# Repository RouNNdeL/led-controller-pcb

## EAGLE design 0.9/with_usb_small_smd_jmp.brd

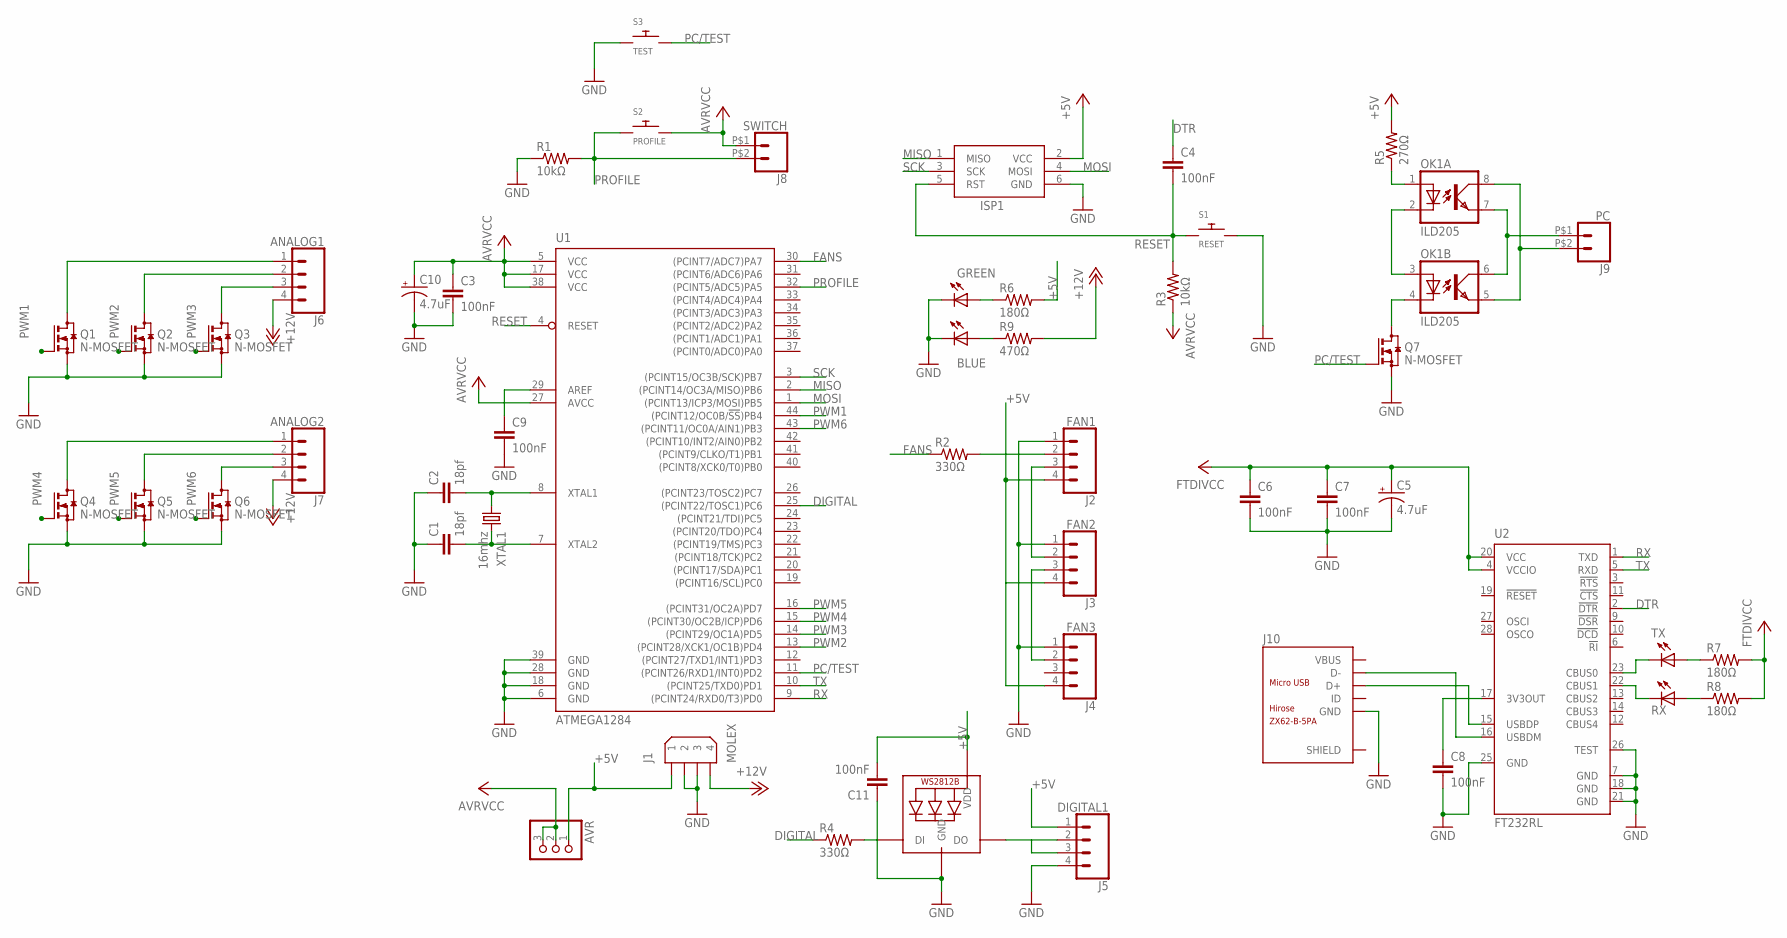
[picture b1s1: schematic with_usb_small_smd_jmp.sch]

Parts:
AVR: PINHD-1X3; 1X03
C1, C2: 18pf; C0805
C3, C4, C6, C7, C8, C9, C11: 100nF; C0805
C5, C10: 4.7uF; 153CLV-0405
ISP1: AVRISP-6; AVRISP
J1: MOLEX; 9090-4R
J2: FAN1; TJC8-4P
J3: FAN2; TJC8-4P
J4: FAN3; TJC8-4P
J5: DIGITAL1; MX-22-05-3041
J6: ANALOG1; MX-22-05-3041
J7: ANALOG2; MX-22-05-3041
J8: SWITCH; MX-7395-02BG
J9: PC; MX-7395-02BG
J10: MICRO_USB
LED1: TX; SML0805
LED2: RX; SML0805
LED3: GREEN; SML0805
LED4: BLUE; SML0805
OK1: ILD205; SOIC08
Q1, Q2, Q3, Q4, Q5, Q6, Q7: N-MOSFET; SOT23
R1, R3: 10kΩ; R0805
R2, R4: 330Ω; R0805
R5: 270Ω; R0805
R6, R7, R8: 180Ω; R0805
R9: 470Ω; R0805
RGB: WS2812B
S1: RESET; B3F-1000
S2: PROFILE; B3F-1000
S3: TEST; B3F-1000
U1: ATMEGA1284; TQFP44
U2: FT232RL; SSOP28
XTAL1: 16mhz; HC49U-V

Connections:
+3V3: C8.1, U2.17 (3V3OUT)
+5V: AVR.1, C5.+, C6.1, C7.1, C11.2, J1.1, J2.4, J3.4, J4.4, J5.1, R5.2, R6.2, R7.2, R8.2, RGB.1-VDD (VDD), U2.4 (VCCIO), U2.20 (VCC)
+12V: J1.4, J6.4, J7.4, R9.2
AVR: AVR.2, AVR.3, C3.1, C10.+, ISP1.2 (VCC), J8.P$1 (1), R3.1, S2.3, S2.4, U1.5 (VCC), U1.17 (VCC), U1.27 (AVCC), U1.38 (VCC)
D+: J10.3 (D+), U2.15 (USBDP)
D-: J10.2 (D-), U2.16 (USBDM)
DIGITAL: R4.1, U1.25 ((PCINT22/TOSC1)PC6)
DIN-D: J5.2, J5.3, RGB.2-DOUT (DO)
DTR: C4.1, U2.2 (!DTR)
F1-DIN: J2.2, R2.2
F2-DIN: J2.3, J3.2
F3-DIN: J3.3, J4.2
FANS: R2.1, U1.30 ((PCINT7/ADC7)PA7)
GND: C1.1, C2.1, C3.2, C5.-, C6.2, C7.2, C8.2, C9.2, C10.-, C11.1, ISP1.6 (GND), J1.2, J1.3, J2.1, J3.1, J4.1, J5.4, J10.5 (GND), LED3.C, LED4.C, Q1.2 (S), Q2.2 (S), Q3.2 (S), Q4.2 (S), Q5.2 (S), Q6.2 (S), Q7.2 (S), R1.1, RGB.3-GND (GND), S1.3, S1.4, S3.1, S3.2, U1.6 (GND), U1.18 (GND), U1.28 (GND), U1.39 (GND), U2.7 (GND), U2.18 (GND), U2.21 (GND), U2.25 (GND), U2.26 (TEST)
LED-IN: R4.2, RGB.4-DIN (DI)
MISO: ISP1.1 (MISO), U1.2 ((PCINT14/OC3A/MISO)PB6)
MOSI: ISP1.4 (MOSI), U1.1 ((PCINT13/ICP3/MOSI)PB5)
unnamed: LED1.A, R7.1
unnamed: LED2.A, R8.1
unnamed: LED4.A, R9.1
unnamed: C9.1, U1.29 (AREF)
unnamed: LED3.A, R6.1
unnamed: OK1.1 (A), R5.1
unnamed: OK1.2 (C), OK1.3 (A)
unnamed: OK1.4 (C), Q7.3 (D)
PC1: J9.P$2 (2), OK1.5 (EMIT), OK1.8 (COL)
PC2: J9.P$1 (1), OK1.6 (COL), OK1.7 (EMIT)
PC/TEST: Q7.1 (G), S3.3, S3.4, U1.11 ((PCINT26/RXD1/INT0)PD2)
PROFILE: J8.P$2 (2), R1.2, S2.1, S2.2, U1.32 ((PCINT5/ADC5)PA5)
PWM1: Q1.1 (G), U1.44 ((PCINT12/OC0B/!SS!)PB4)
PWM2: Q2.1 (G), U1.13 ((PCINT28/XCK1/OC1B)PD4)
PWM3: Q3.1 (G), U1.14 ((PCINT29/OC1A)PD5)
PWM4: Q4.1 (G), U1.15 ((PCINT30/OC2B/ICP)PD6)
PWM5: Q5.1 (G), U1.16 ((PCINT31/OC2A)PD7)
PWM6: Q6.1 (G), U1.43 ((PCINT11/OC0A/AIN1)PB3)
RESET: C4.2, ISP1.5 (RST), R3.2, S1.1, S1.2, U1.4 (RESET)
RX: U1.9 ((PCINT24/RXD0/T3)PD0), U2.1 (TXD)
RXLED: LED2.C, U2.22 (CBUS1)
S1-1: J6.1, Q1.3 (D)
S1-2: J6.2, Q2.3 (D)
S1-3: J6.3, Q3.3 (D)
S2-1: J7.1, Q4.3 (D)
S2-2: J7.2, Q5.3 (D)
S2-3: J7.3, Q6.3 (D)
SCK: ISP1.3 (SCK), U1.3 ((PCINT15/OC3B/SCK)PB7)
TX: U1.10 ((PCINT25/TXD0)PD1), U2.5 (RXD)
TXLED: LED1.C, U2.23 (CBUS0)
XTAL1: C2.2, U1.8 (XTAL1), XTAL1.1
XTAL2: C1.2, U1.7 (XTAL2), XTAL1.2

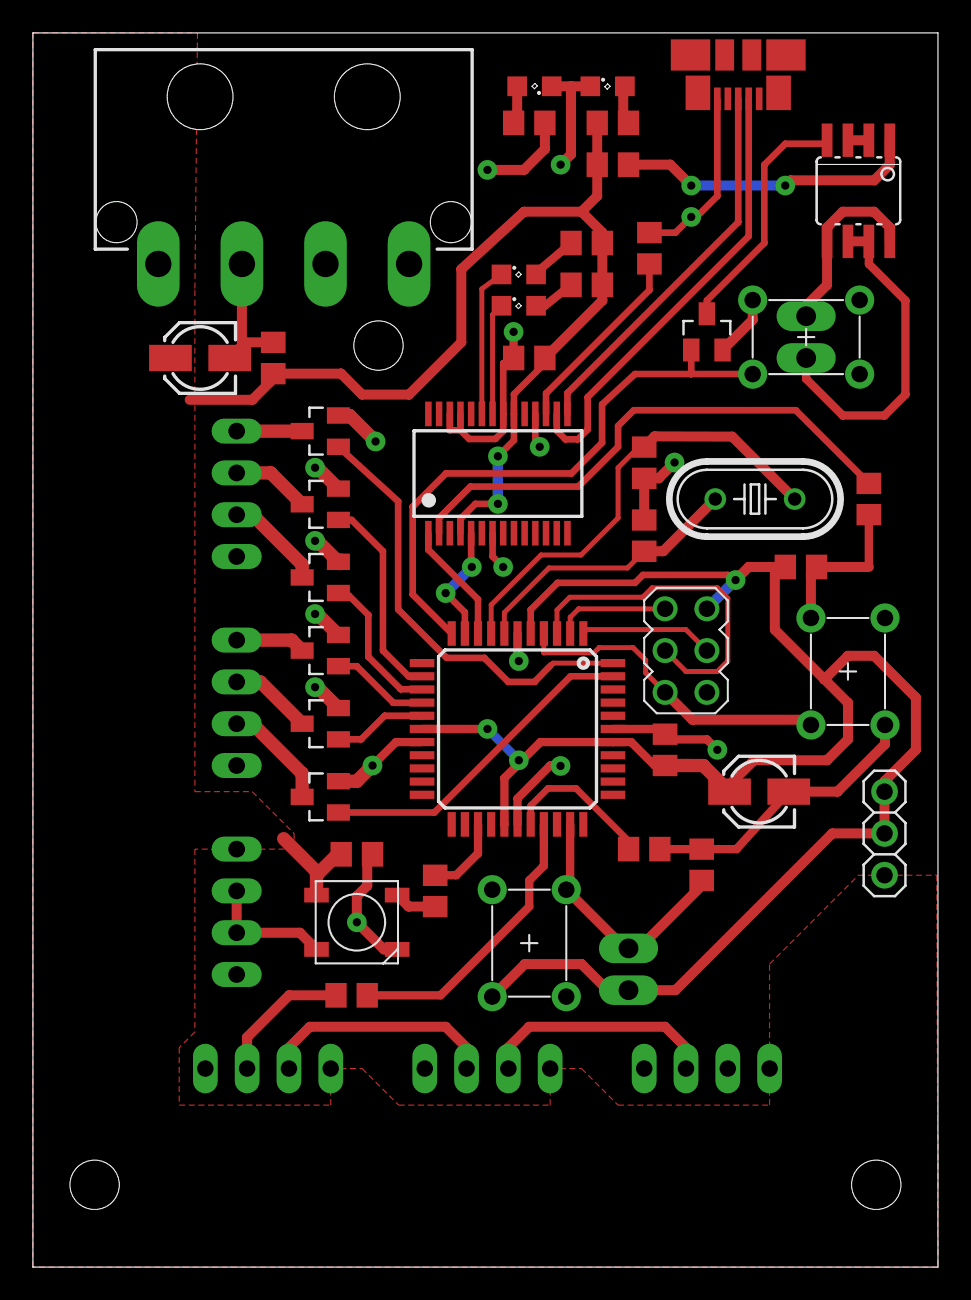
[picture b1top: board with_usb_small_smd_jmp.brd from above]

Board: 2 copper layers, 55.0 x 75.0 mm, 51 parts (0 on the bottom side), 49 nets.

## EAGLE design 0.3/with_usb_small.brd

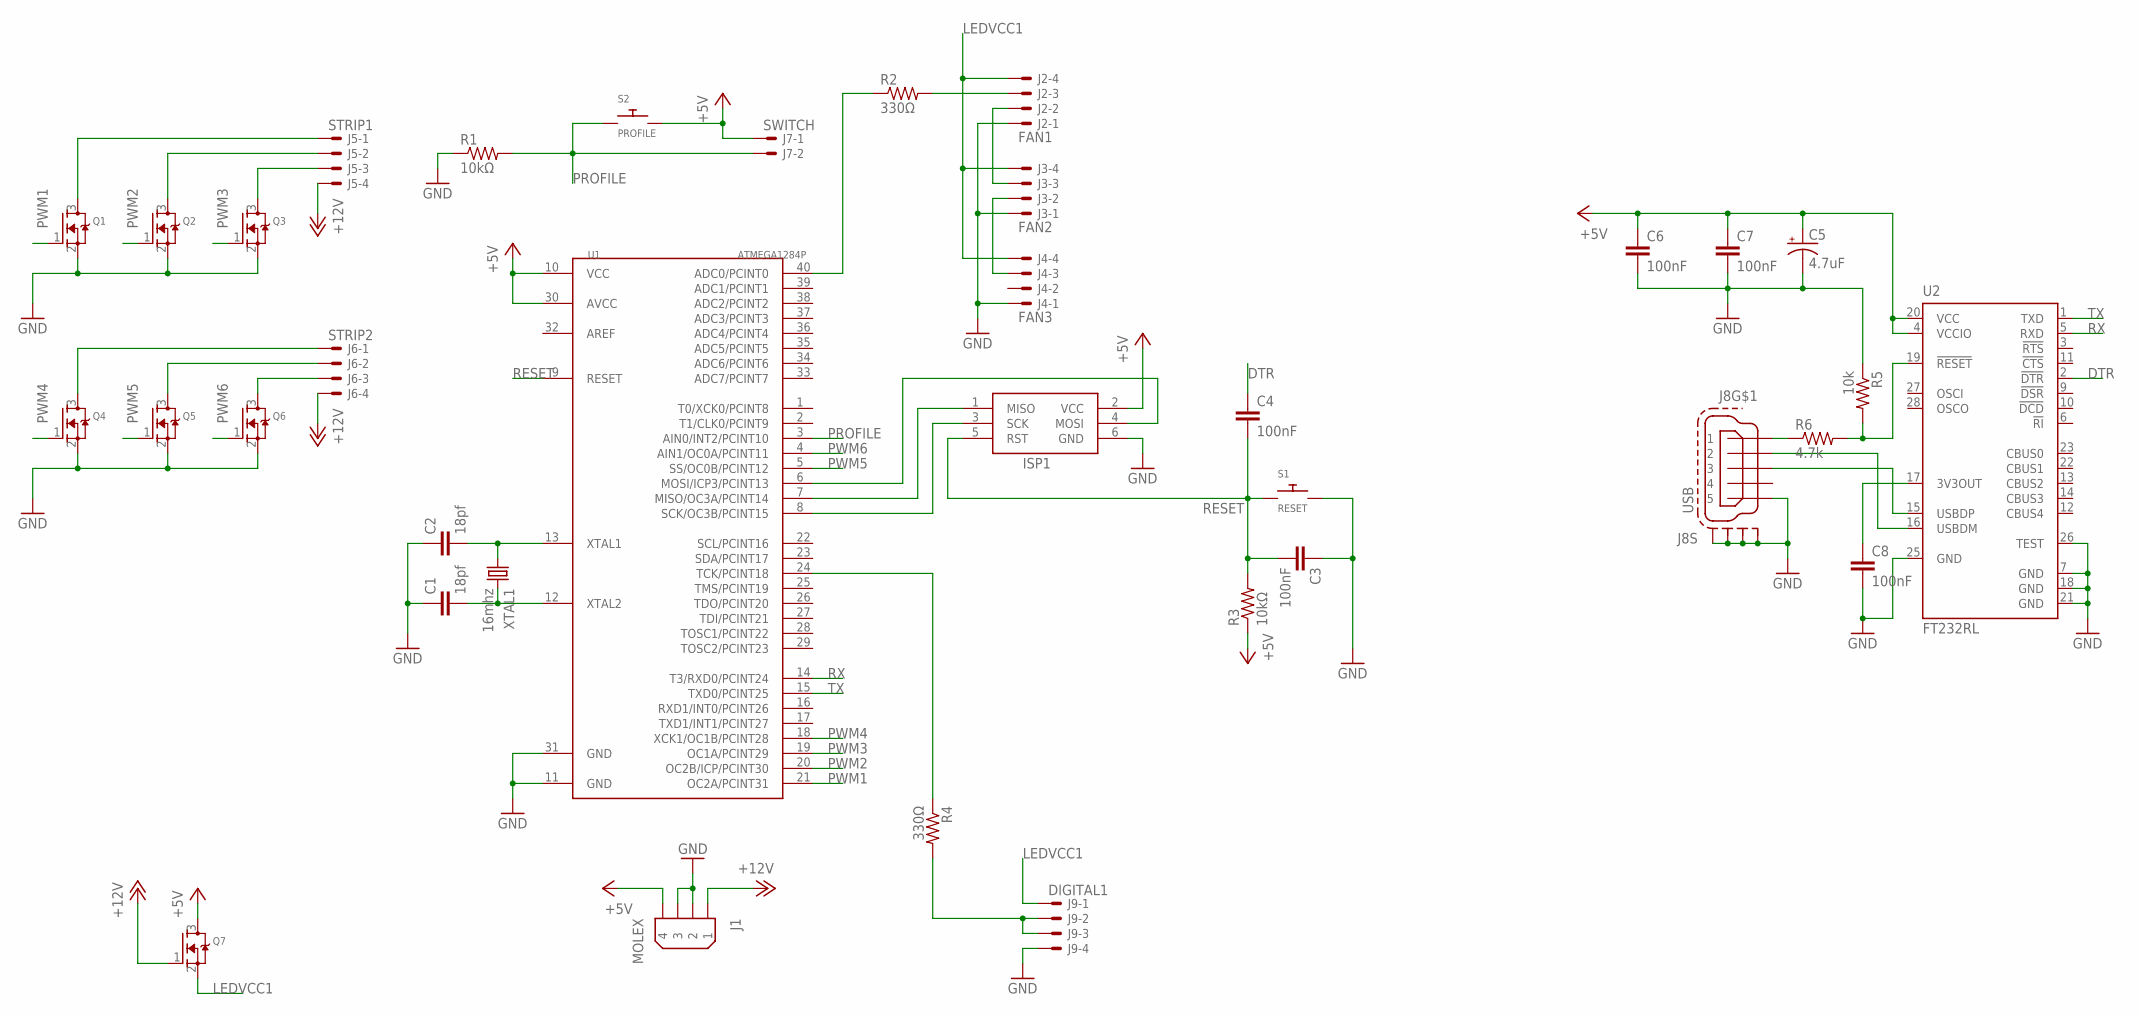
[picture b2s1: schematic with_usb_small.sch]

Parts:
C1, C2: 18pf; C0805
C3, C4, C6, C7, C8: 100nF; C0805
C5: 4.7uF; 153CLV-0505
ISP1: AVRISP-6; AVRISP
J1: MOLEX; 9090-4R
J2: FAN1; 22-23-2041
J3: FAN2; 22-23-2041
J4: FAN3; 22-23-2041
J5: STRIP1; 22-23-2041
J6: STRIP2; 22-23-2041
J7: SWITCH; 22-23-2021
J8: USB; 32005-201
J9: DIGITAL1; 22-23-2041
Q1, Q2, Q3, Q4, Q5, Q6, Q7: MOSFET-NREFLOW; SOT23
R1, R3: 10kΩ; M0805
R2, R4: 330Ω; M0805
R5: 10k; R0805
R6: 4.7k; R0805
S1: RESET; B3F-1000
S2: PROFILE; B3F-1000
U1: ATMEGA1284P; DIL40
U2: FT232RL; SSOP28
XTAL1: 16mhz; HC49U-V

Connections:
+5V: C5.+, C6.1, C7.1, ISP1.2 (VCC), J1.4, J7.1, Q7.3 (D), R3.1, S2.3, S2.4, U1.10 (VCC), U1.30 (AVCC), U2.4 (VCCIO), U2.20 (VCC)
+12V: J1.1, J5.4, J6.4, Q7.1 (G)
D+: J8.3, U2.15 (USBDP)
D-: J8.2, U2.16 (USBDM)
DIN-D: J9.2, J9.3, R4.2
DTR: C4.1, U2.2 (!DTR)
F1-DIN: J2.3, R2.2
F2-DIN: J2.2, J3.3
F3-DIN: J3.2, J4.3
GND: C1.1, C2.1, C3.1, C5.-, C6.2, C7.2, C8.2, ISP1.6 (GND), J1.2, J1.3, J2.1, J3.1, J4.1, J8.5, J8.M1 (S1), J8.M2 (S2), J8.M3 (S3), J8.M4 (S4), J9.4, Q1.2 (S), Q2.2 (S), Q3.2 (S), Q4.2 (S), Q5.2 (S), Q6.2 (S), R1.1, R5.1, S1.3, S1.4, U1.11 (GND), U1.31 (GND), U2.7 (GND), U2.18 (GND), U2.21 (GND), U2.25 (GND), U2.26 (TEST)
LEDVCC1: J2.4, J3.4, J4.4, J9.1, Q7.2 (S)
MISO: ISP1.1 (MISO), U1.7 (MISO/OC3A/PCINT14)
MOSI: ISP1.4 (MOSI), U1.6 (MOSI/ICP3/PCINT13)
unnamed: C8.1, U2.17 (3V3OUT)
unnamed: R2.1, U1.40 (ADC0/PCINT0)
unnamed: R5.2, R6.2, U2.19 (!RESET)
unnamed: R4.1, U1.24 (TCK/PCINT18)
PROFILE: J7.2, R1.2, S2.1, S2.2, U1.3 (AIN0/INT2/PCINT10)
PWM1: Q1.1 (G), U1.21 (OC2A/PCINT31)
PWM2: Q2.1 (G), U1.20 (OC2B/ICP/PCINT30)
PWM3: Q3.1 (G), U1.19 (OC1A/PCINT29)
PWM4: Q4.1 (G), U1.18 (XCK1/OC1B/PCINT28)
PWM5: Q5.1 (G), U1.5 (SS/OC0B/PCINT12)
PWM6: Q6.1 (G), U1.4 (AIN1/OC0A/PCINT11)
RESET: C3.2, C4.2, ISP1.5 (RST), R3.2, S1.1, S1.2, U1.9 (RESET)
RX: U1.14 (T3/RXD0/PCINT24), U2.5 (RXD)
S1-1: J5.1, Q1.3 (D)
S1-2: J5.2, Q2.3 (D)
S1-3: J5.3, Q3.3 (D)
S2-1: J6.1, Q4.3 (D)
S2-2: J6.2, Q5.3 (D)
S2-3: J6.3, Q6.3 (D)
SCK: ISP1.3 (SCK), U1.8 (SCK/OC3B/PCINT15)
TX: U1.15 (TXD0/PCINT25), U2.1 (TXD)
USBVCC: J8.1, R6.1
XTAL1: C2.2, U1.13 (XTAL1), XTAL1.1
XTAL2: C1.2, U1.12 (XTAL2), XTAL1.2

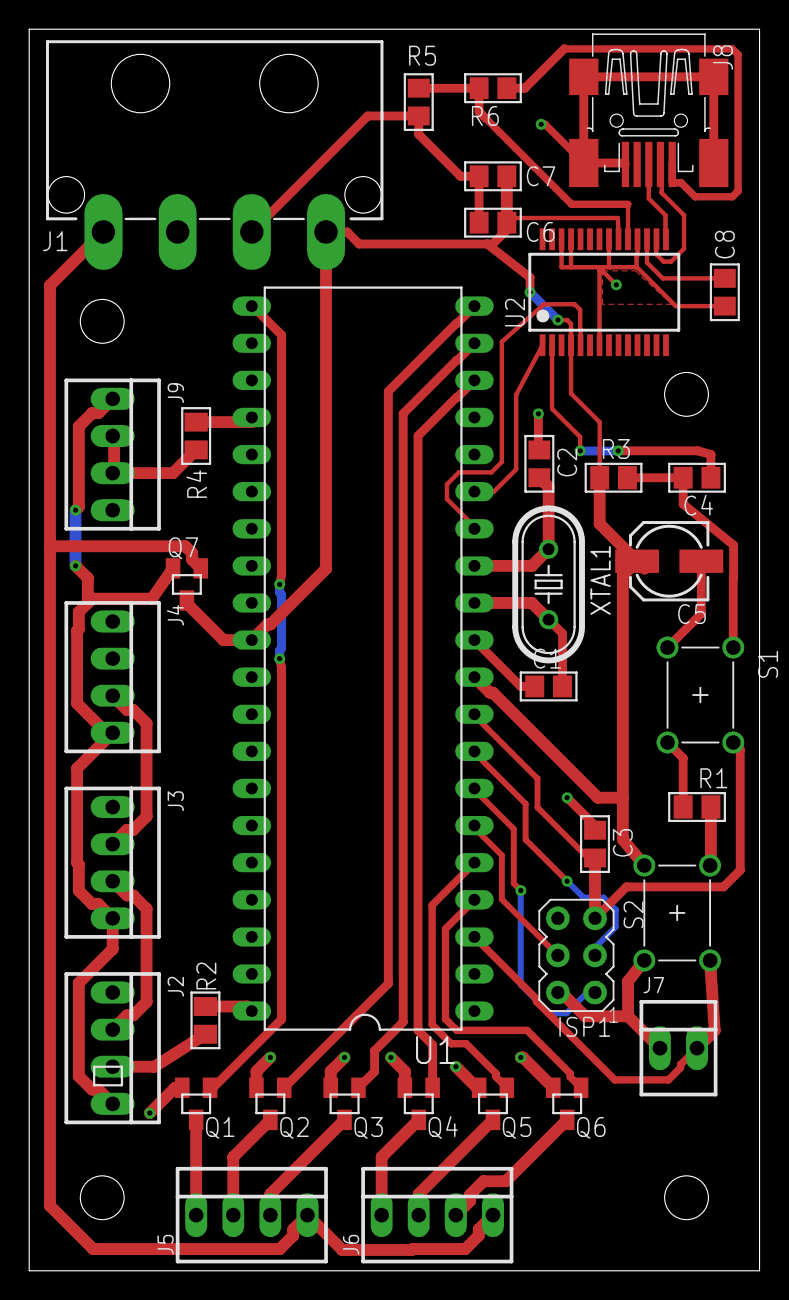
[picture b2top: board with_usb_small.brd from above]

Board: 2 copper layers, 50.0 x 85.0 mm, 36 parts (0 on the bottom side), 37 nets.

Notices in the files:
0.9/with_usb_small_smd_jmp.brd:
© 2017 Krzysztof Zdulski
